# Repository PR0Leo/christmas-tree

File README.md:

# Become an Engineer for a Day
unter dem Motto veranstaltet die Firma Work-Microwave ein 2.5 Tage Praktikum, um Schüler vor allem aus der FOS in Holzkirchen einen Einblick in das Leben eines Ingeneurs zu zeigen. wie vielfälltig wir arbeiten.
## Ziele für die Schüler
oder was die Beschreibung auf der Webseite sagt, um was es geht:
- **Mitmachen und Ausprobieren:** Du wirst anhand eines Beispiels den Ablauf eines Entwicklungsprojektes kennenlernen!
- **Hands-on Erfahrungen:** Teste den Prototypen, analysiere Ergebnisse und lerne, wie wir Probleme lösen.
- **Teamwork:** Arbeite mit unseren coolen Ingenieuren zusammen, nimm an Meetings teil und bring deine eigenen Ideen ein.
- **Verschiedene Bereiche entdecken:** Du wirst in dem Entwicklungsprojekt alle Bereiche – von Schaltplanerstellung über Layout und Bestückung bis zu Softwareentwicklung und Test – kennenlernen.
- **Und das Beste:**  Am Ende darfst du dein selbst entwickeltes Projekt mit nach Hause nehmen – als Erinnerung an deine praktische Erfahrung!
What we it says we offer: 
- **Echte Einblicke:** Du erfährst, wie der Alltag eines Ingenieurs aussieht und kannst dein Wissen in der Praxis anwenden
- **Mentoren, die helfen:**Unsere erfahrenen Ingenieure sind für dich da und leiten Dich Schritt für Schritt an
- **Coole Atmosphäre:** Bei uns herrscht ein freundliches und offenes Arbeitsklima, in dem du dich wohlfühlst
## Ziele vom Author(LRO)
1. Schüler für EIT (electrical Engineering) zu inspirieren.
2. Das sich die Schüler hier Bewerben wollen.
Zweiteres schafft man durch ersteres und weniger, aber gezielter Werbung.
### Was macht ein Ingenieur (zum Ingenieur)?
Kommuniziert ehrlich was es heißt ein Ingenieur zu sein. Indem man die Vorteile davon wie im nächsten Abschnitt erwähnt während der 2.5 Tage, inspiriert man die Schüler dadurch.
- Selbständiges Arbeiten
- Datenblätter lesen
- Weiterbilden (Theorie lernen)
- Teamarbeit
- Abstraktionsfähigkeit, Blackbox denken
- Praxisorientiert arbeiten - erschaffen.

### Was sind die Vorteile als Ingenieur bei der Firma Work Microwave zu arbeiten?
- Erschaffer - dadurch fühle ich mich erfüllt.
- Vertrauen und Verantwortung durch großen Einfluss auf Projekte, indem man viel Verantwortung überschrieben bekommt fühlt man sich Gebraucht und das macht einen Glücklich. Der Gedanke, dass ich mit meiner Arbeit dazu beitrage die Menscheitsgeschichte auf einen neuen Stand der Kommunikation bringen kann mit Lasertechnologie quer durch den Orbit.
- Vorteil bei WM: Einblick in viele Bereiche
## Ablauf
| Tag | Aufgabe                                              | Zeit                          |
| --- | ---------------------------------------------------- | ----------------------------- |
| 1.  | Einführung                                           |9-10:30 Uhr (1.5h)            |
|     | Projekteinführung                                    | - 12 Uhr (1.5h)              |
|     | Mittagsessen                                         | - 13 Uhr (1h)                 |
|     | Schaltplan erstellen                                 | - 14:30 Uhr (1.5h)            |
|     | Layout fertigstellen                                 | - 16 Uhr (1.5h)               |
|  2. | Löten                                                | 9 - 10 Uhr (1h) 
|     | Produktion anschauen                                 | 10 - 10.30 Uhr (0.5h)               |
|     | Montage                                              | - 11 Uhr (0.5h) |
|     | Puffer                                               | - 12 Uhr (1h) |
|     | Mittagsessen                                         | 12 - 13 Uhr (1h)              |
|     | Programmier Einführung                               | - 14 Uhr (1h)            |
|     | Programmier Aufgaben lösen                           | - 15.30 Uhr (1.5h)           |
|     | Flashen                                              | - 16:00 Uhr (0.5h)           |
| 3.  | Freies Arbeite                                       | 9 - 11.15 Uhr (2.25h)           |
|     | Abschluss                                            | - 12 Uhr (0.75h)               |
|     | Mittagsessen                                         | - 12:45 Uhr (0.75h)           |
## Inhalt
Einführung: 
- Kennenlernen
- Wissenstand Abfragen
- Firmenvorstellung 
- Rundgang

Projekteinführung:
- Prototyp Aufbau mit Theory

Schaltplan(Mentor Projekt findet man unter: X:\\LRO\):
- Stiftleisten(Arduino) hinzufügen 
- Bauteile auswählen dazu
- Datenblätter lesen von Lautsprecher, Amplifier, NTC 
- mit Spannungsteiler Berechnung für NTC 
- alles hinzufügen und verbinden.

Layout fertigstellen:
- Bauteile platzieren.
- Routing auf zwei Lagen kennenlernen.

Löten:
- Arduino Stiftleisten Löten 
- Problembehebung + Stiftleiste von Weihnachtsbaum löten

Produktion anschauen nach Löten, um Vorteil zu sehen.

Montage von Lautsprecher und Füßen:
2 x Schrauben (M7985-2.0x14A)
2 x Mutter (M0934-2.0-A)
6 x Beilagscheibe (M0125A-2.0-A)
4 x Schraube (M7985-2.0x0.6-A)
4 x Abstandshalter (M-DIST1_M2.0x05)

Puffer:
- Falls Schaltplan oder Layout länger dauert kann man Layout auch 1h lang noch in der Früh machen.
- oder auf Wünsche, Fragen eingehen.
- Ansonsten schon mit programmieren anfangen.

Programmier Einführung:
- Schwerpunkt Arduino IDE, aber VSC mit PIO (PlatformIO) zeigen oder gleich PIO, wenn Arduino schon bekannt.
- Code Struktur verstehen und somit lesen können (Link_zu_Arbeitsmaterial).
- Extra: kurze Bit Einführung => Verständnis für Magic Number 255.

Programmier Aufgaben:
- Farbe dimmen und mischen bei der If Abfrage für den NTC Licht Effekt
- oder If Abfrage komplett selber schreiben.
- restlichen Programm grob durchgehen um Bedinung des Weihnachtsbaums zu verstehen.

Hausaufgabe: gewünschte Songs als MP3 privat runterladen.

Freies Arbeiten:
- Schüler Ideen verfolgen zum Programmieren oder PCB design.
- LED Effekte hinzufügen: Regenbogen, gelber Stern an die Spitze, 
- Songs draufspielen mittels SD Card Writer.
- Uhr hinzufügen und Zeitgesteuert arbeiten.

Abschluss
- Übergabe des Weihnachtsbaum an den Schüler.
- Zusammenfassen was man gelernt hat - mit was einen Ingenieur ausmacht verknüpfen.
- Flyer verteilen und gezieltes Recruting abhängig vom Wunsch der Schüler erstellen:
    Nach Wunsch - Dual Student, Ausbildung in den verschiedenen Bereichen oder Praktikum anbieten.

Abschlussessen
- Weihnachtsbäume an Tisch stellen und Musik abspielen.

# To Do
- Links hinzufügen
- Mentor vorbereiten
- Bild von Code Tutorial hinzufügen
- Review
- Einführungs Präsentation mit Prototype hinzufügen
- Mit Recruting sprechen: Wer und in welchen Umfang man das Recruiting macht. 

# Vorbereitung

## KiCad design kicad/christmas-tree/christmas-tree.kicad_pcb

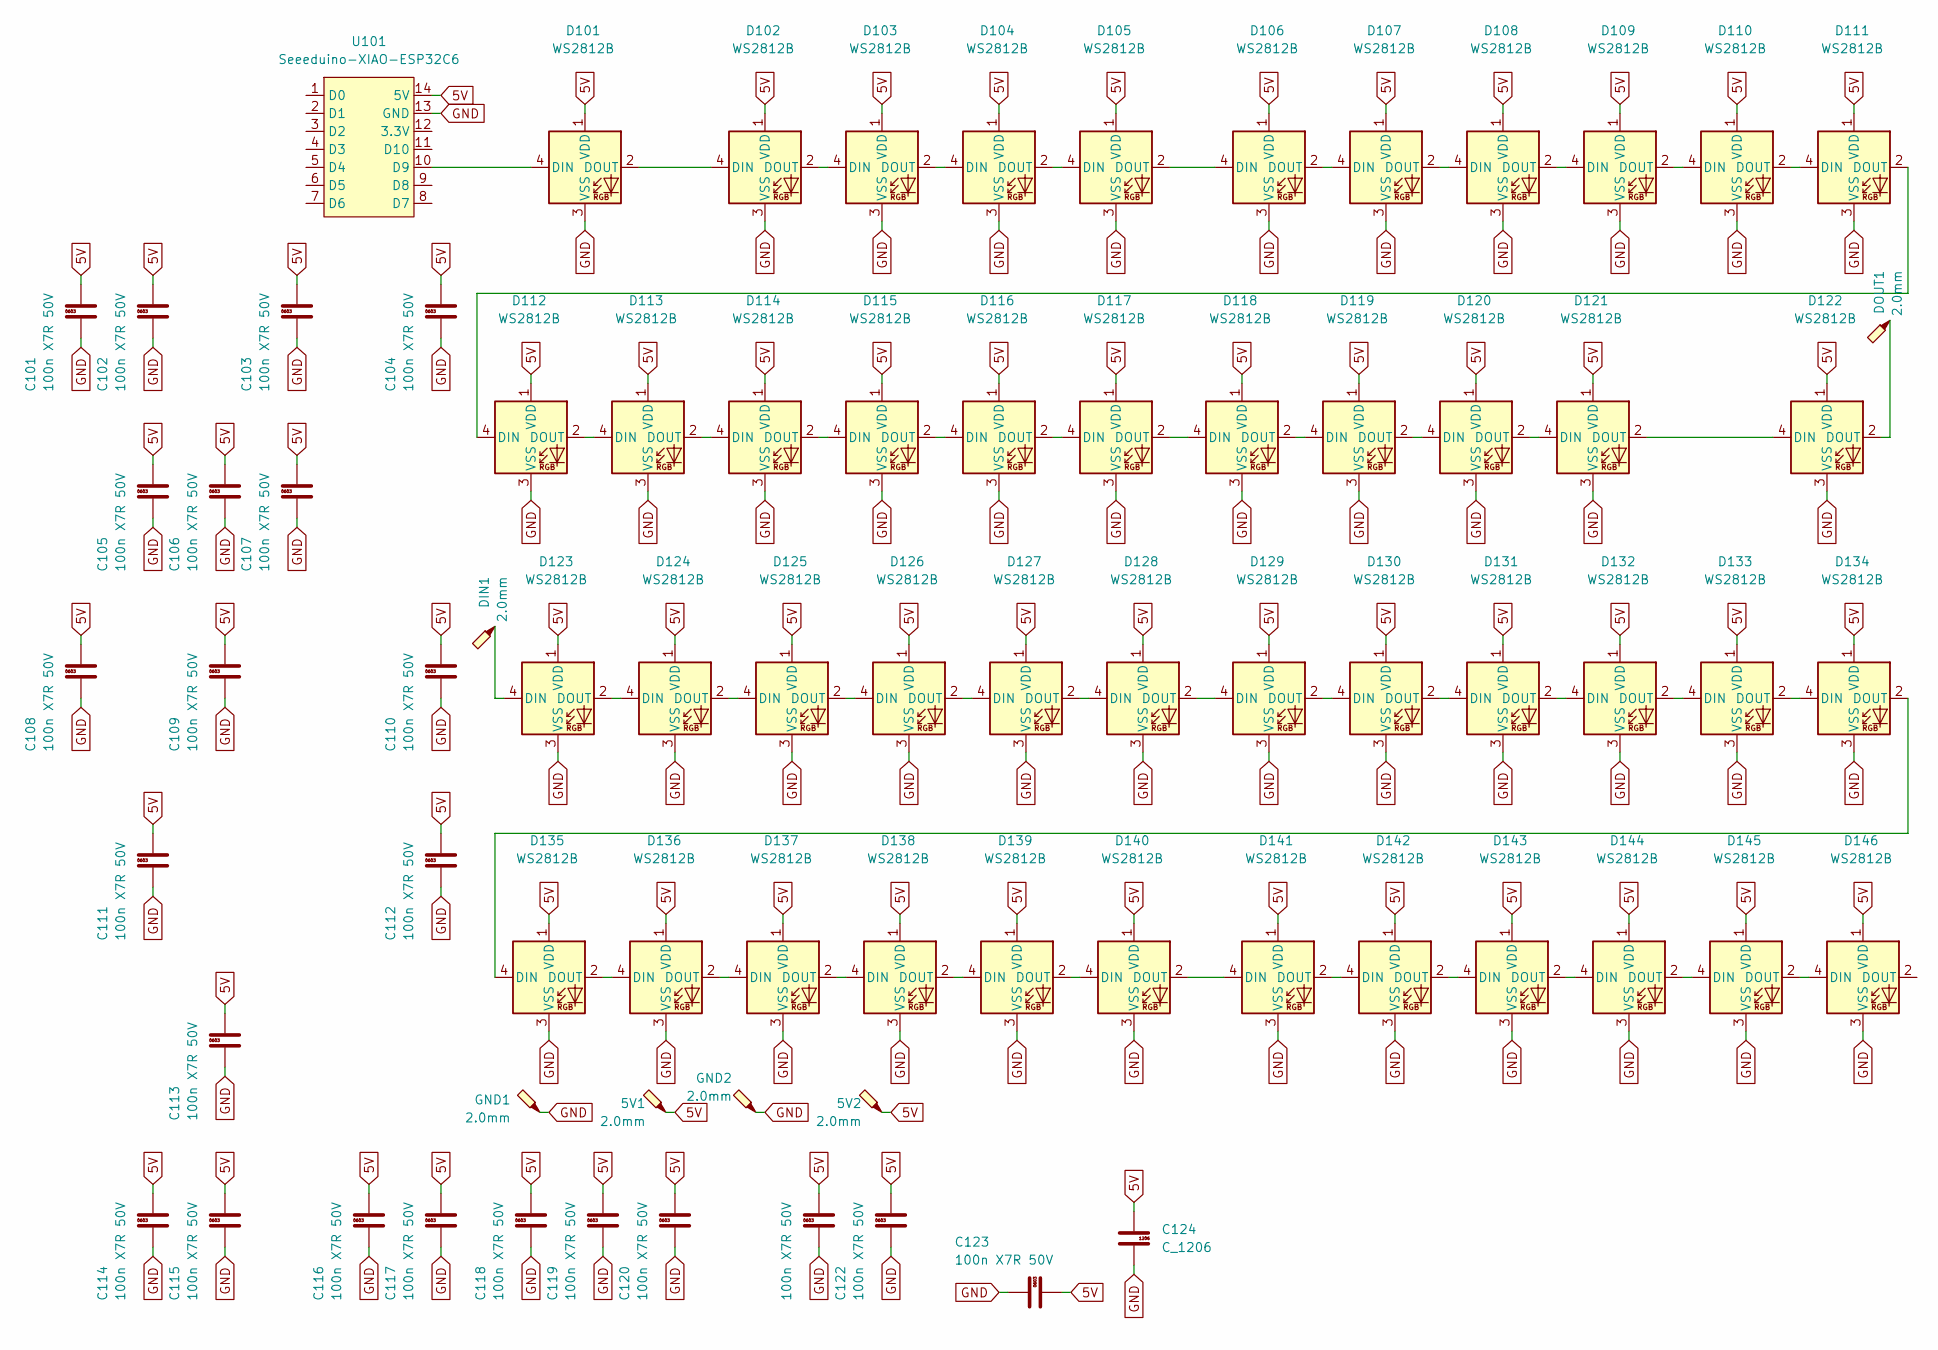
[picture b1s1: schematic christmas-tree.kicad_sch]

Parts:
5V1, 5V2: 2.0mm; TestPad_2.0mm
C101, C102, C103, C104, C105, C106, C107, C108, C109, C110, C111, C112, C113, C114, C115, C116, C117, C118, C119, C120, C121, C122, C123: 100n X7R 50V; R_0603_1608Metric; Farnell 2310603
C124: C_1206; C_1206_3216Metric_Pad1.33x1.80mm_HandSolder
D101, D102, D103, D104, D105, D106, D107, D108, D109, D110, D111, D112, D113, D114, D115, D116, D117, D118, D119, D120, D121, D122, D123, D124, D125, D126, D127, D128, D129, D130, D131, D132, D133, D134, D135, D136, D137, D138, D139, D140, D141, D142, D143, D144, D145, D146: WS2812B; LED_WS2812B_PLCC4_5.0x5.0mm_P3.2mm
DIN1: 2.0mm; TestPad_2.0mm
DOUT1: 2.0mm; TestPad_2.0mm
GND1, GND2: 2.0mm; TestPad_2.0mm
U101: Seeeduino-XIAO-ESP32C6

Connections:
5V: 5V1.1, 5V2.1, C101.2, C102.2, C103.2, C104.2, C105.2, C106.2, C107.2, C108.2, C109.2, C110.2, C111.2, C112.2, C113.2, C114.2, C115.2, C116.2, C117.2, C118.2, C119.2, C120.2, C121.2, C122.2, C123.2, C124.1, D101.1 (VDD), D102.1 (VDD), D103.1 (VDD), D104.1 (VDD), D105.1 (VDD), D106.1 (VDD), D107.1 (VDD), D108.1 (VDD), D109.1 (VDD), D110.1 (VDD), D111.1 (VDD), D112.1 (VDD), D113.1 (VDD), D114.1 (VDD), D115.1 (VDD), D116.1 (VDD), D117.1 (VDD), D118.1 (VDD), D119.1 (VDD), D120.1 (VDD), D121.1 (VDD), D122.1 (VDD), D123.1 (VDD), D124.1 (VDD), D125.1 (VDD), D126.1 (VDD), D127.1 (VDD), D128.1 (VDD), D129.1 (VDD), D130.1 (VDD), D131.1 (VDD), D132.1 (VDD), D133.1 (VDD), D134.1 (VDD), D135.1 (VDD), D136.1 (VDD), D137.1 (VDD), D138.1 (VDD), D139.1 (VDD), D140.1 (VDD), D141.1 (VDD), D142.1 (VDD), D143.1 (VDD), D144.1 (VDD), D145.1 (VDD), D146.1 (VDD), U101.14 (5V)
GND: C101.1, C102.1, C103.1, C104.1, C105.1, C106.1, C107.1, C108.1, C109.1, C110.1, C111.1, C112.1, C113.1, C114.1, C115.1, C116.1, C117.1, C118.1, C119.1, C120.1, C121.1, C122.1, C123.1, C124.2, D101.3 (VSS), D102.3 (VSS), D103.3 (VSS), D104.3 (VSS), D105.3 (VSS), D106.3 (VSS), D107.3 (VSS), D108.3 (VSS), D109.3 (VSS), D110.3 (VSS), D111.3 (VSS), D112.3 (VSS), D113.3 (VSS), D114.3 (VSS), D115.3 (VSS), D116.3 (VSS), D117.3 (VSS), D118.3 (VSS), D119.3 (VSS), D120.3 (VSS), D121.3 (VSS), D122.3 (VSS), D123.3 (VSS), D124.3 (VSS), D125.3 (VSS), D126.3 (VSS), D127.3 (VSS), D128.3 (VSS), D129.3 (VSS), D130.3 (VSS), D131.3 (VSS), D132.3 (VSS), D133.3 (VSS), D134.3 (VSS), D135.3 (VSS), D136.3 (VSS), D137.3 (VSS), D138.3 (VSS), D139.3 (VSS), D140.3 (VSS), D141.3 (VSS), D142.3 (VSS), D143.3 (VSS), D144.3 (VSS), D145.3 (VSS), D146.3 (VSS), GND1.1, GND2.1, U101.13 (GND)
unnamed: D101.4 (DIN), U101.10 (D9)
unnamed: D101.2 (DOUT), D102.4 (DIN)
unnamed: D102.2 (DOUT), D103.4 (DIN)
unnamed: D103.2 (DOUT), D104.4 (DIN)
unnamed: D104.2 (DOUT), D105.4 (DIN)
unnamed: D105.2 (DOUT), D106.4 (DIN)
unnamed: D106.2 (DOUT), D107.4 (DIN)
unnamed: D107.2 (DOUT), D108.4 (DIN)
unnamed: D108.2 (DOUT), D109.4 (DIN)
unnamed: D109.2 (DOUT), D110.4 (DIN)
unnamed: D110.2 (DOUT), D111.4 (DIN)
unnamed: D111.2 (DOUT), D112.4 (DIN)
unnamed: D112.2 (DOUT), D113.4 (DIN)
unnamed: D113.2 (DOUT), D114.4 (DIN)
unnamed: D114.2 (DOUT), D115.4 (DIN)
unnamed: D115.2 (DOUT), D116.4 (DIN)
unnamed: D116.2 (DOUT), D117.4 (DIN)
unnamed: D117.2 (DOUT), D118.4 (DIN)
unnamed: D118.2 (DOUT), D119.4 (DIN)
unnamed: D119.2 (DOUT), D120.4 (DIN)
unnamed: D120.2 (DOUT), D121.4 (DIN)
unnamed: D121.2 (DOUT), D122.4 (DIN)
unnamed: D122.2 (DOUT), DOUT1.1
unnamed: D123.4 (DIN), DIN1.1
unnamed: D123.2 (DOUT), D124.4 (DIN)
unnamed: D124.2 (DOUT), D125.4 (DIN)
unnamed: D125.2 (DOUT), D126.4 (DIN)
unnamed: D126.2 (DOUT), D127.4 (DIN)
unnamed: D127.2 (DOUT), D128.4 (DIN)
unnamed: D128.2 (DOUT), D129.4 (DIN)
unnamed: D129.2 (DOUT), D130.4 (DIN)
unnamed: D130.2 (DOUT), D131.4 (DIN)
unnamed: D131.2 (DOUT), D132.4 (DIN)
unnamed: D132.2 (DOUT), D133.4 (DIN)
unnamed: D133.2 (DOUT), D134.4 (DIN)
unnamed: D134.2 (DOUT), D135.4 (DIN)
unnamed: D135.2 (DOUT), D136.4 (DIN)
unnamed: D136.2 (DOUT), D137.4 (DIN)
unnamed: D137.2 (DOUT), D138.4 (DIN)
unnamed: D138.2 (DOUT), D139.4 (DIN)
unnamed: D139.2 (DOUT), D140.4 (DIN)
unnamed: D140.2 (DOUT), D141.4 (DIN)
unnamed: D141.2 (DOUT), D142.4 (DIN)
unnamed: D142.2 (DOUT), D143.4 (DIN)
unnamed: D143.2 (DOUT), D144.4 (DIN)
unnamed: D144.2 (DOUT), D145.4 (DIN)
unnamed: D145.2 (DOUT), D146.4 (DIN)

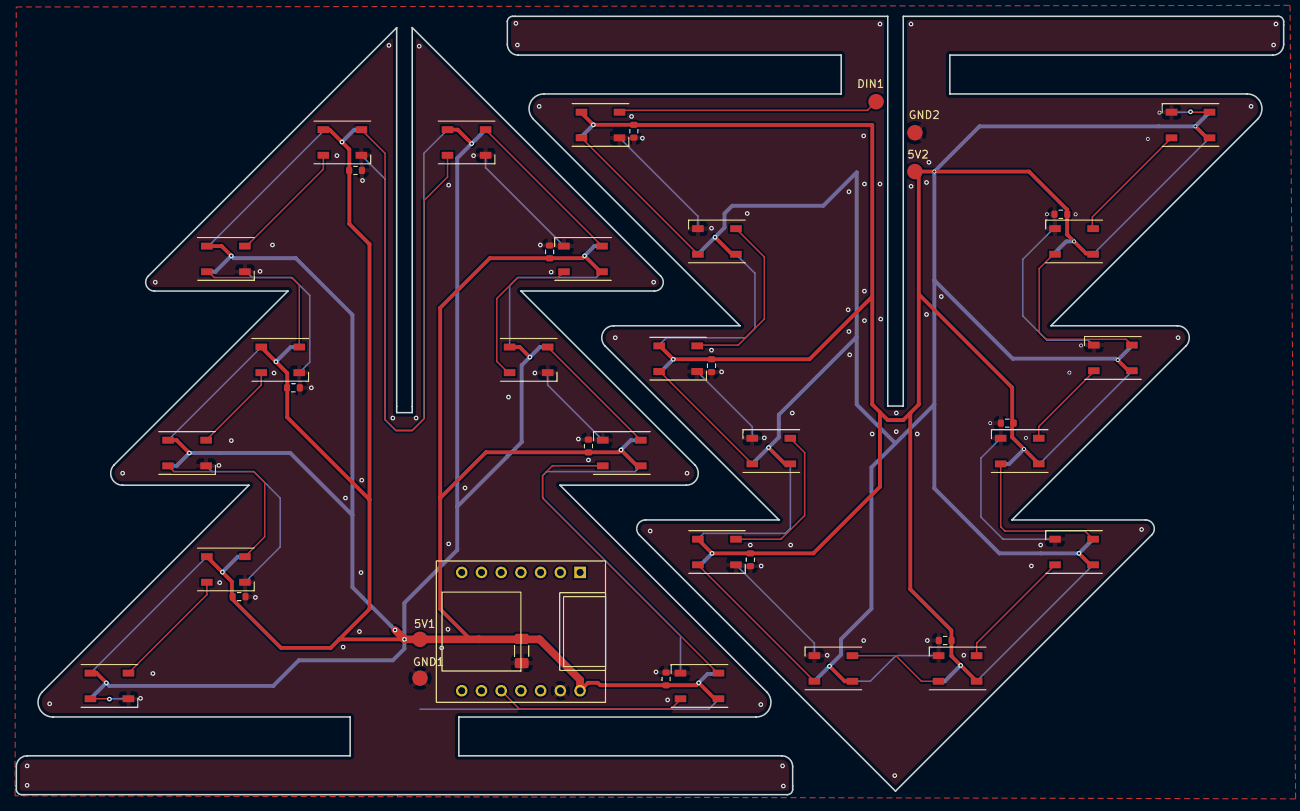
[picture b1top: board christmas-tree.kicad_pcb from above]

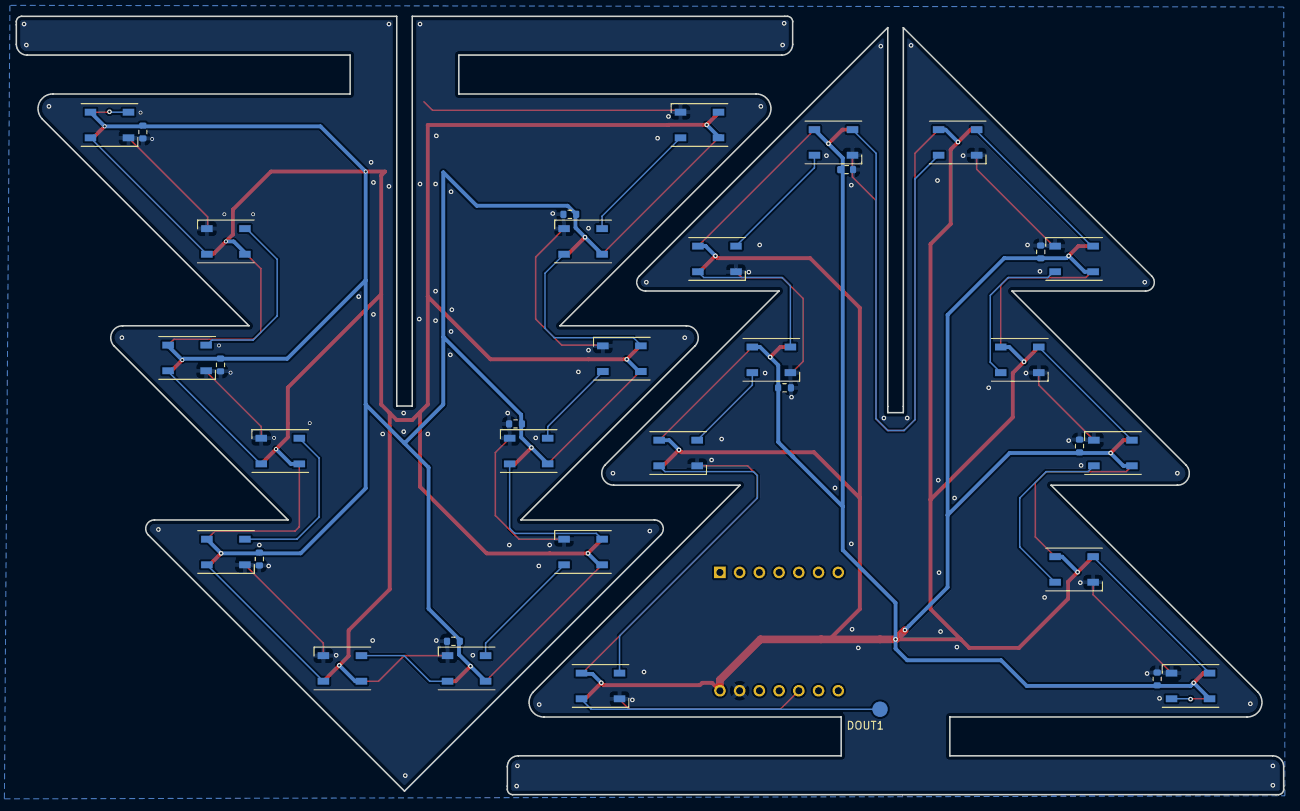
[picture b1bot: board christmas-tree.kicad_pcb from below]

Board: 2 copper layers, 163.2 x 100.3 mm, 77 parts (35 on the bottom side), 49 nets.

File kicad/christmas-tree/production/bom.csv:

Designator,Footprint,Quantity,Value,LCSC Part #
"C101, C102, C103, C104, C105, C106, C107, C108, C109, C110, C111, C112, C113, C114, C115, C116, C117, C118, C119, C120, C121, C122, C123",0603,23,100n X7R 50V,C14663
C124,1206,1,C_1206,
"D101, D102, D103, D104, D105, D106, D107, D108, D109, D110, D111, D112, D113, D114, D115, D116, D117, D118, D119, D120, D121, D122, D123, D124, D125, D126, D127, D128, D129, D130, D131, D132, D133, D134, D135, D136, D137, D138, D139, D140, D141, D142, D143, D144, D145, D146",LED_WS2812B_PLCC4_5.0x5.0mm_P3.2mm,46,WS2812B,
U101,Seeeduino-XIAO-ESP32C6,1,Seeeduino-XIAO-ESP32C6,

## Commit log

2025-10-21 gettingStarted
2025-10-21 test
2025-10-21 sorted
2025-10-24 copytoWM
2025-10-28 READMEtest
2025-10-28 deletedREADME
2025-10-28 updateWM
